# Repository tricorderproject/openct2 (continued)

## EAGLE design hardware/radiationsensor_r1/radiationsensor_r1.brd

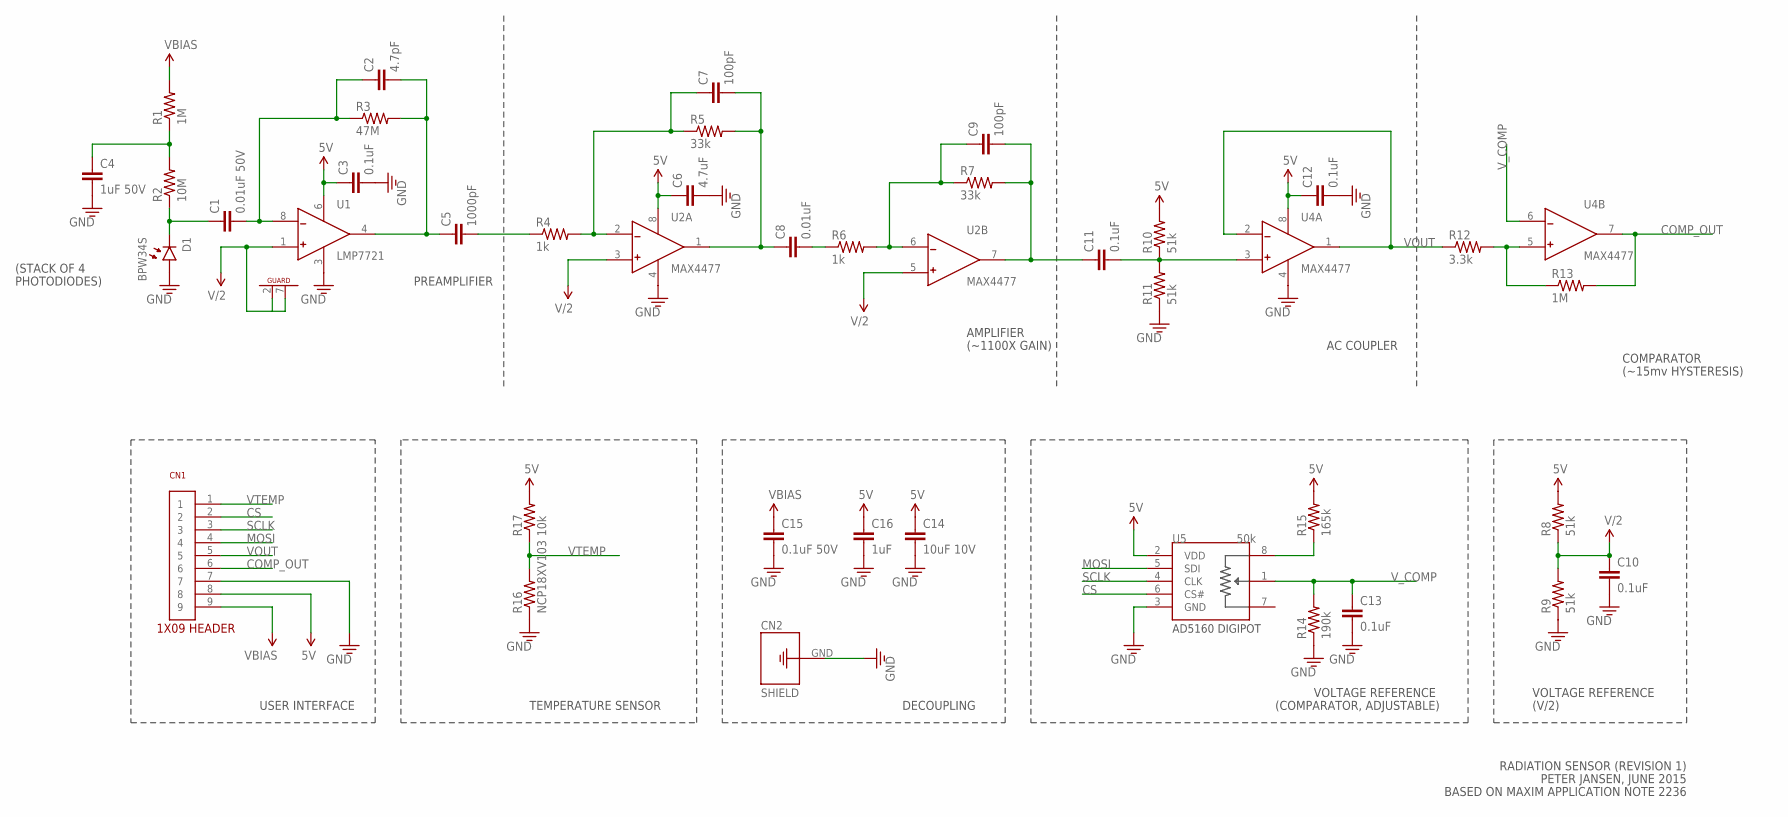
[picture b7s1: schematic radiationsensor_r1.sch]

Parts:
C1: 0.01uF 50V; 0603
C2: 4.7pF; 0603
C3, C10, C11, C12, C13: 0.1uF; 0603
C4: 1uF 50V; 0603
C5: 1000pF; 0603
C6: 4.7uF; 0603
C7, C9: 100pF; 0603
C8: 0.01uF; 0603
C14: 10uF 10V; 0805
C15: 0.1uF 50V; 0603
C16: 1uF; 0603
CN1: 1X09
CN2: GROUND-PAD
D1: BPW34S; BPW34S-4STACK-SIDEMOUNT
R1, R13: 1M; 0603
R2: 10M; 0603
R3: 47M; 0603
R4, R6: 1k; 0603
R5, R7: 33k; 0603
R8, R9, R10, R11: 51k; 0603
R12: 3.3k; 0603
R14: 190k; 0603
R15: 165k; 0603
R16: NCP18XV103; 0603
R17: 10k; 0603
U1: LMP7721; SOIC-8
U2, U4: MAX4477; SOIC-8
U5: 50k; SOT-23-8

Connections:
5V: C3.1, C6.1, C12.1, C14.1, C16.1, CN1.8, R8.2, R10.2, R15.2, R17.2, U1.6 (VCC), U2.8 (V+), U4.8 (V+), U5.2 (VDD)
COMP_OUT: CN1.6, R13.2, U4.7 (OUT)
CS: CN1.2, U5.6 (CS#)
GND: C3.2, C4.2, C6.2, C10.2, C12.2, C13.2, C14.2, C15.2, C16.2, CN1.7, CN2.GND, D1.A (ANODE), R9.1, R11.1, R14.1, R16.1, U1.3 (GND), U2.4 (V-), U4.4 (V-), U5.3 (GND)
MOSI: CN1.4, U5.5 (SDI)
unnamed: C1.2, C2.1, R3.1, U1.8 (-)
unnamed: C1.1, D1.C (CATHODE), R2.1
unnamed: C7.2, C8.1, R5.2, U2.1 (OUT)
unnamed: C4.1, R1.1, R2.2
unnamed: C7.1, R4.2, R5.1, U2.2 (-)
unnamed: C5.2, R4.1
unnamed: C2.2, C5.1, R3.2, U1.4 (OUT)
unnamed: C9.1, R6.2, R7.1, U2.6 (-)
unnamed: C8.2, R6.1
unnamed: C11.2, R10.1, R11.2, U4.3 (+)
unnamed: C9.2, C11.1, R7.2, U2.7 (OUT)
unnamed: R12.2, R13.1, U4.5 (+)
unnamed: R15.1, U5.8 (A)
SCLK: CN1.3, U5.4 (CLK)
V/2: C10.1, R8.1, R9.2, U1.1 (+), U1.2 (G1), U1.7 (G2), U2.3 (+), U2.5 (+)
VBIAS: C15.1, CN1.9, R1.2
VOUT: CN1.5, R12.1, U4.1 (OUT), U4.2 (-)
VTEMP: CN1.1, R16.2, R17.1
V_COMP: C13.1, R14.2, U4.6 (-), U5.1 (W)

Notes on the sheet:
PREAMPLIFIER
AMPLIFIER
AC COUPLER
COMPARATOR
VOLTAGE REFERENCE
(V/2)
(COMPARATOR, ADJUSTABLE)
USER INTERFACE
(~15mv HYSTERESIS)
(~1100X GAIN)
DECOUPLING
TEMPERATURE SENSOR
PETER JANSEN, JUNE 2015
RADIATION SENSOR (REVISION 1)
BASED ON MAXIM APPLICATION NOTE 2236
(STACK OF 4
PHOTODIODES)

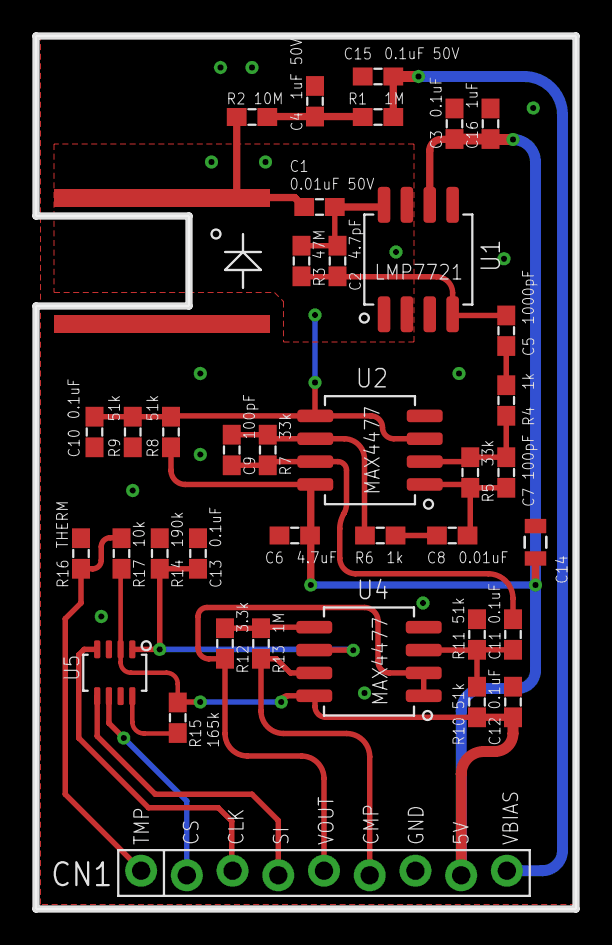
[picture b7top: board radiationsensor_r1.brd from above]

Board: 2 copper layers, 30.0 x 48.5 mm, 40 parts (1 on the bottom side), 24 nets.

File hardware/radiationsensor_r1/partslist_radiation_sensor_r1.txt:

Partlist																						Part	Value	Device	Package		QTY per board		# of boards		QTY total		Digikey #											C1	0.01uF	50V	CAP0603		1		18		18		445-16165-1-ND"C10, *"	0.1uF	50V	603		6		18		108		311-1344-1-NDC5	1000pF	CAP0603	603		1		18		18		445-5736-1-ND"C7, C9"	100pF	CAP0603	603		2		18		36		1276-2159-1-NDC14	10uF	10V	805		1		18		18		490-3886-1-ND"C4, C16"	1uF	50V	603		2		18		36		445-7468-1-NDC2	2.2pF	50V	603		1		18		18		399-8791-1-NDC6	4.7uF	CAP0603	603		1		18		18		1276-1784-1-ND											CN1	1X09	MALE RIGHTANGLE	1X09		1		18		18		S1111EC-09-ND											D1	BPW34S	PHOTODIODE4STACK-SIDEMOUNT	BPW34S-4STACK-SIDEMOUNT		4		18		72		BPW34S-ND											R17	10k	RESISTOR0603	603		1		18		18		P10.0KHCT-NDR2	10M	RESISTOR0603	603		1		18		18		541-10MAYCT-NDR15	165k	RESISTOR0603	603		1		18		18		P165KHCT-NDR14	190k	RESISTOR0603	603		1		18		18		P191KHCT-ND"R4, R6"	1k	RESISTOR0603	603		2		18		36		P1.00KHCT-ND"R1, R13"	1M	RESISTOR0603	603		2		18		36		P1.00MHCT-NDR12	3.3k	RESISTOR0603	603		1		18		18		P3.30KHCT-ND"R5, R7"	33k	RESISTOR0603	603		2		18		36		P33.0KHCT-NDR3	47M	RESISTOR0603	603		1		18		18		541-47MAHCT-ND"R10, R9, R10, R11"	51k	RESISTOR0603	603		4		18		72		P51.0KHCT-NDR16	NCP18XV103	RESISTOR0603	603		1		18		18		490-6944-1-ND											U1	LMP7721	OPAMP-LMP7721	SOIC-8		1		18		18		LMP7721MA/NOPB-ND"U2, U4"	MAX4477	OPAMP-MAX4477	SOIC-8		2		18		36		MAX4477ASA+-NDU5	50k	AD5160	SOT-23-8		1		18		18		AD5160BRJZ50-RL7CT-ND											Other											Stranded Wire for Ground Shield					1		1		1		CN100B-25-NDRoll of Aluminum Tape											Hardware Store

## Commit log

2015-03-18 Added initial Eagle library
2015-03-18 cleanup
2015-03-18 Added photodiode and precision opamps to library
2015-03-18 Added beginnings of radiation detector schematic
2015-03-19 Added PIC microcontroller
2015-03-19 Added photodiode preamplifier
2015-04-29 Added first revision of radiation sensor design
2015-04-29 Added pdf of schematic
2015-06-05 Starting radiation sensor rev1
2015-06-05 minor cleanup
2015-06-05 minor changes
2015-06-06 radiation sensor r1 layout nearly complete
2015-06-07 schematic and board cleanup
2015-06-07 Added part in library for radiation sensor rev1
2015-06-07 Added beginnings of 2.25inch dia parallel array board
2015-06-07 Progress on array board/schematic
2015-06-07 Added breakout pattern to array
2015-06-07 breakout pattern cleanup
2015-06-07 basic layout (not including microcontroller)
2015-06-08 Added connector an IO expander
2015-06-08 connector and IO expander nearly wired
2015-06-08 basic layout complete
2015-06-08 started board outline and ground plane
2015-06-09 Board outline and ground planes complete
2015-06-09 mechanical bits
2015-06-09 final cleanup
2015-06-09 Added shield connection to radiation sensor rev1
2015-06-09 Minor clearance change to array board
2015-06-10 schematic cleanup
2015-06-10 Added gerbers and images for radiationsensor r1 and arrayboard r0
2015-06-13 progressing towards a second draft of the structural bits
2015-06-14 Added microcontroller board rev0
2015-06-15 completed first rework of structure
2015-06-18 added PDFs of schematics
2015-06-21 Added jig to bend photodiode pins to 20 degrees
2015-06-27 Added partslist for Radiation Sensor r1
2015-07-09 Added rough mechanical layout for imaging array board rev1
2015-07-10 partial routing for imaging array rev1
2015-07-10 additional routing
2015-07-11 finished routing for imaging array board rev1
2015-07-11 Added imaging array rev1 gerbers and pdf schematic
2015-08-05 Added microcontroller rev1 board
2015-09-07 Various additions from being forgetful at committing regularly
2015-09-07 Initial commits of detector platform and table bearing holder
2015-09-07 Added new version of mechanical base
2015-09-07 Removed previous version of mechanical base
2015-09-07 Initial source mount design and modifications to detector platform to mount it
2015-10-10 Added stepper controller firmware
2015-10-10 Added imaging array firmware
2015-12-03 Added structural files that I forgot to commit a while ago
2015-12-12 Mounts for electronics (pi, arduino, relay, usb hub) in bottom of unit
2016-01-01 Beginning main power supply board
2016-01-01 more basic placement and shape
2016-01-01 basic placement
2016-01-02 component layout complete
2016-01-02 major routing on power supply board
2016-01-02 ground plane routing
2016-01-02 cleanup and silkscreen
2016-01-02 Added power supply rev0 gerbers and images
2016-01-02 Added power supply partslist
2016-01-07 Added limit switch sketchup and STL file for Z axis
2016-01-08 minor changes to powersuppy partslist
2016-01-10 Added instructions for installing java, scala, and sbt
2016-01-10 Added instructions for installing IntelliJ IDEA
2016-01-11 Added initial port of the SSD1351 display driver to the Raspberry Pi 2 with the wiringPi library
2016-01-12 Added OLED navigation screen for raspberry pi
2016-01-12 Added navigation screen interface board for the raspberry pi 2
2016-01-14 Added gerbers and images for navigation screen boards
2016-01-30 minor change to OLED pins
2016-02-14 Added latest structural parts
2016-02-14 Added first prototype of keyed table
2016-02-14 Added mount point for navigation screen prototype
2016-02-23 Added URL to project build logs
2016-03-13 Added nutholder and shield mount sketchup files
2016-03-13 Added shield mount STL file
2016-03-14 added radiation shield between source and detectors
2016-03-14 Added mount holes for cabling to structural plates
2016-03-15 minor mechanical change to shield mount
2016-03-20 Added Z limit switches to StepperController
2016-03-27 Minor changes -- added limit switch monitor to StepperController, and Python serial test
2016-03-28 Beginnings of calibration program
2016-03-28 added bug output
2016-03-28 Added text files showing led bug
2016-03-30 Minor changes -- calibration test now outputs to file. Long runs seem to freeze -- likely an issue with the waitForResponse() serial function, and timing
2016-03-31 Added timeout/error detection and automatic retries to serial code for python detector calibration script
2016-03-31 Added initial calibration data without source, 3 minutes without source, 8 detectors, scanning over 20 digipot values
2016-03-31 Added calibration run with 5 minute samples at 2 second chunks, for 20 digipot values (170-151)
2016-04-01 Added first calibration data with and without source
2016-04-26 Added VBIAS relay to steppercontroller, and fixed bug in digipot addressing for imagingarray
2016-04-26 added sample calibration data
2016-04-26 Added digipot calibration levels
2016-04-27 Added acquire.py, a command line tool for data acquisition
2016-04-27 Added sample data with table/cube, sampled for 300s, 10 levels
2016-04-28 added (partial) test data
2016-04-28 Additional sample data
2016-04-28 added summary_image.py tool, to convert from detector samples to a basic table summarizing the counts per (zLoc, rLoc), per detector, in counts per minute
2016-05-01 Added rotational data for cube
2016-05-01 Added baseline after test3 rotational measurements
